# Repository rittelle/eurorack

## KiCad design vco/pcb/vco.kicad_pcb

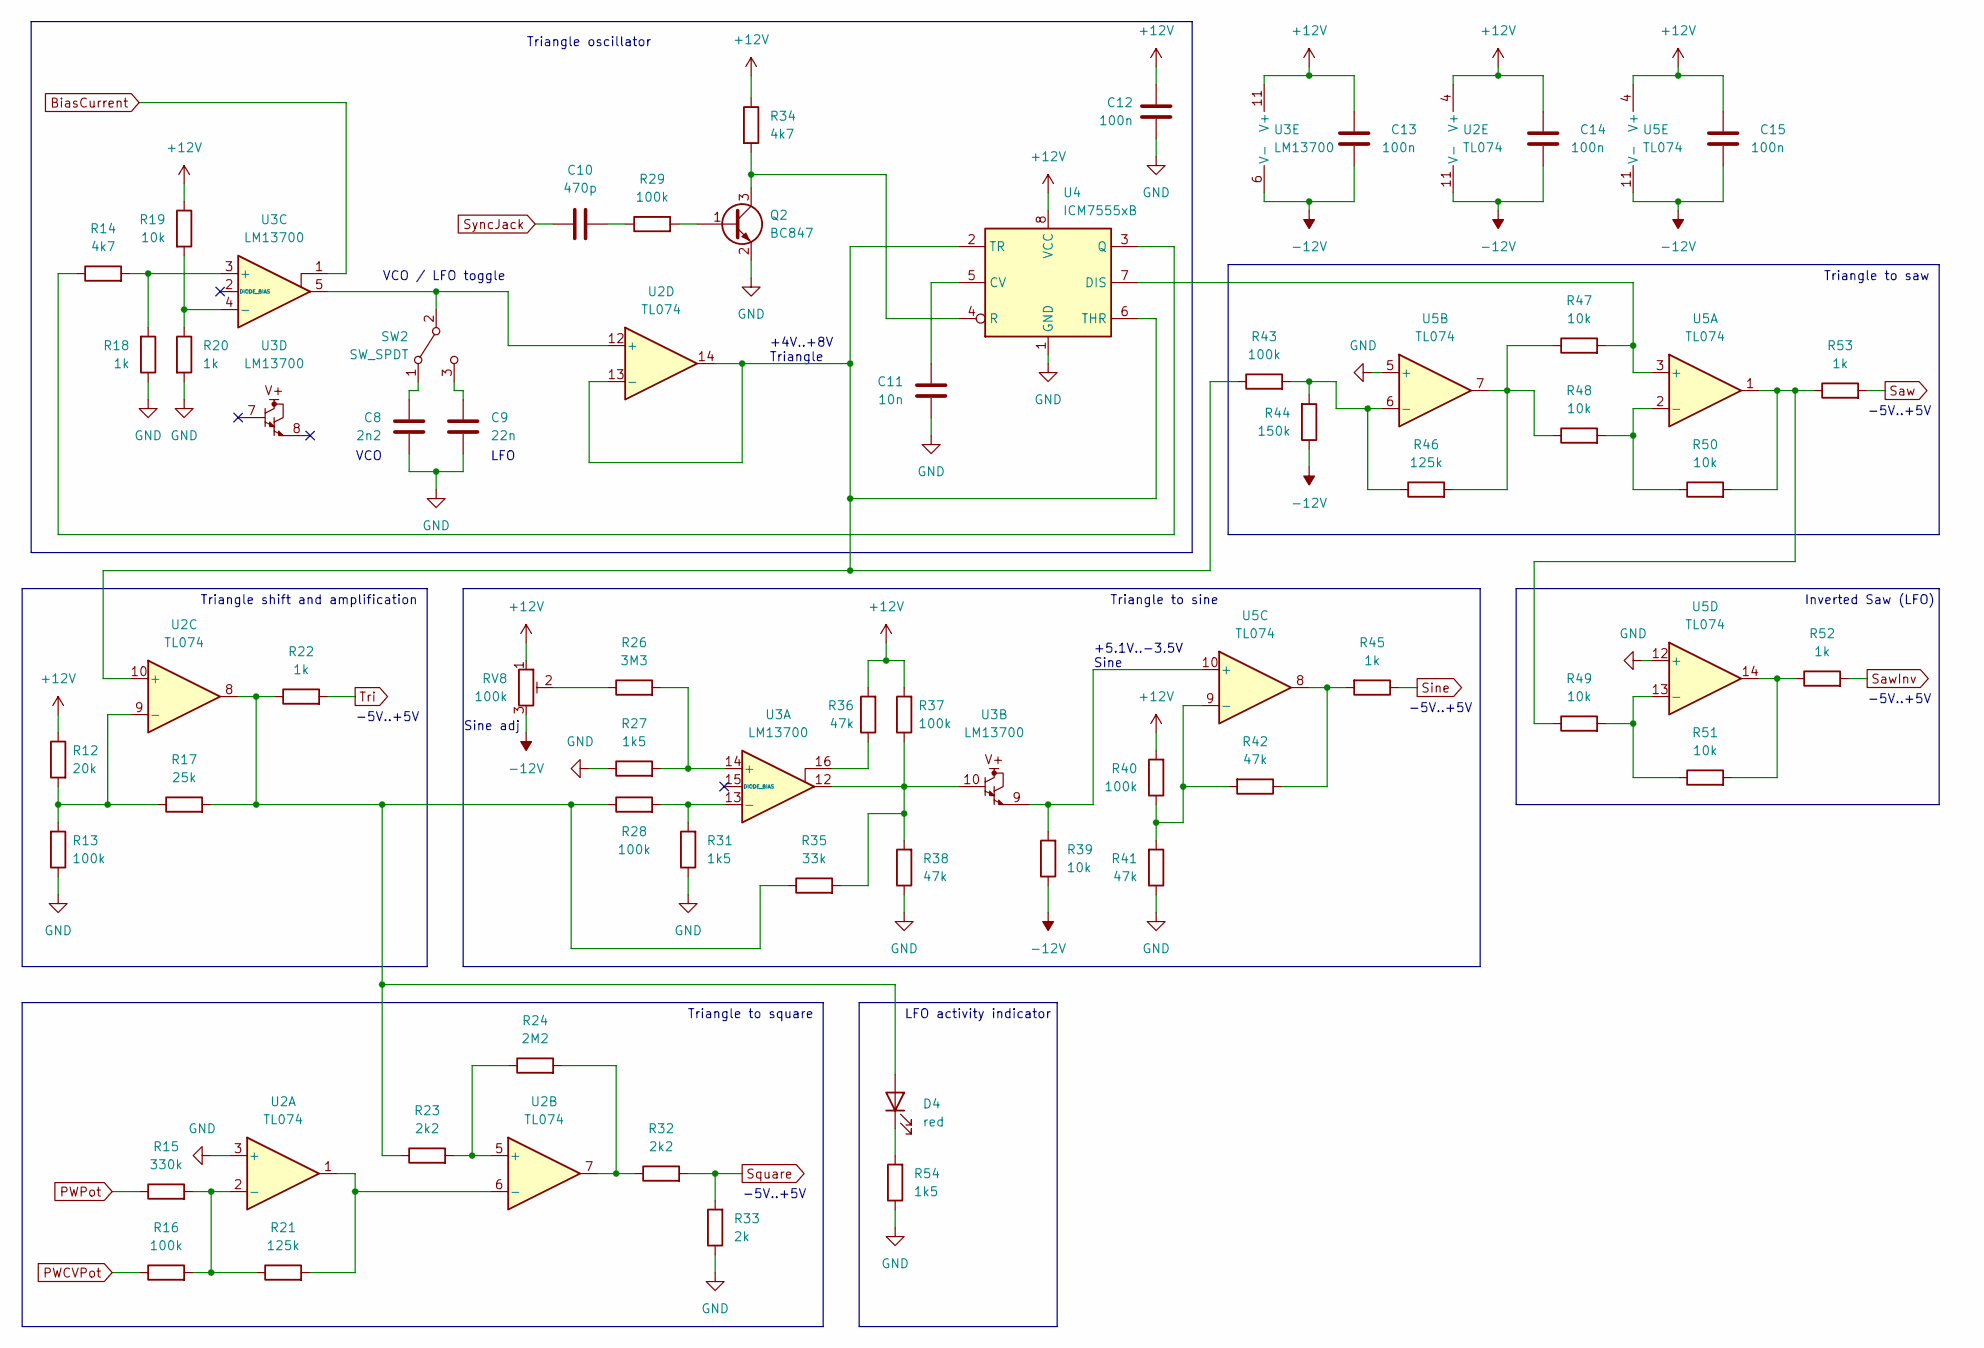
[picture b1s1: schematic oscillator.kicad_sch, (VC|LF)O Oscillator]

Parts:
C8: 2n2; C_0603_1608Metric_Pad1.08x0.95mm_HandSolder
C9: 22n; C_0603_1608Metric_Pad1.08x0.95mm_HandSolder
C10: 470p; C_0603_1608Metric_Pad1.08x0.95mm_HandSolder
C11: 10n; C_0603_1608Metric_Pad1.08x0.95mm_HandSolder
C12, C13, C14, C15: 100n; C_0603_1608Metric_Pad1.08x0.95mm_HandSolder
D4: red; LED_D3.0mm_FlatTop; Mouser 604-WP424IDT
Q2: BC847; SOT-23_Handsoldering; Mouser 771-BC847C-T/R
R12: 20k; R_0603_1608Metric_Pad0.98x0.95mm_HandSolder
R13, R16, R28, R29, R37, R40, R43: 100k; R_0603_1608Metric_Pad0.98x0.95mm_HandSolder
R14, R34: 4k7; R_0603_1608Metric_Pad0.98x0.95mm_HandSolder
R15: 330k; R_0603_1608Metric_Pad0.98x0.95mm_HandSolder
R17: 25k; R_0603_1608Metric_Pad0.98x0.95mm_HandSolder
R18, R20, R22, R45, R52, R53: 1k; R_0603_1608Metric_Pad0.98x0.95mm_HandSolder
R19, R39, R47, R48, R49, R50, R51: 10k; R_0603_1608Metric_Pad0.98x0.95mm_HandSolder
R21, R46: 125k; R_0603_1608Metric_Pad0.98x0.95mm_HandSolder
R23, R32: 2k2; R_0603_1608Metric_Pad0.98x0.95mm_HandSolder
R24: 2M2; R_0603_1608Metric_Pad0.98x0.95mm_HandSolder
R26: 3M3; R_0603_1608Metric_Pad0.98x0.95mm_HandSolder
R27, R31, R54: 1k5; R_0603_1608Metric_Pad0.98x0.95mm_HandSolder
R33: 2k; R_0603_1608Metric_Pad0.98x0.95mm_HandSolder
R35: 33k; R_0603_1608Metric_Pad0.98x0.95mm_HandSolder
R36, R38, R41, R42: 47k; R_0603_1608Metric_Pad0.98x0.95mm_HandSolder
R44: 150k; R_0603_1608Metric_Pad0.98x0.95mm_HandSolder
RV8: 100k; Potentiometer_Bourns_3296W_Vertical
SW2: SW_SPDT; Switch_Sub-Minitiature_Vertical
U2, U5: TL074; SOIC-14_3.9x8.7mm_P1.27mm; Mouser 595-TL074CDR
U3: LM13700; SOIC-16_3.9x9.9mm_P1.27mm; Mouser 926-LM13700MX/NOPB
U4: ICM7555xB; SOIC-8_3.9x4.9mm_P1.27mm; Mouser 968-ICM7555IBAZ-T

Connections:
+12V: C12.2, C13.1, C14.1, C15.1, R12.1, R19.1, R34.1, R36.2, R37.2, R40.2, RV8.1, U2.4 (V+), U3.11 (V+), U4.8 (VCC), U5.4 (V+); also elsewhere on the board
-12V: C13.2, C14.2, C15.2, R39.1, R44.1, RV8.3, U2.11 (V-), U3.6 (V-), U5.11 (V-); also elsewhere on the board
BiasCurrent: U3.1; also elsewhere on the board
GND: C8.1, C9.1, C11.1, C12.1, Q2.2 (E), R13.1, R18.1, R20.2, R27.1, R31.1, R33.1, R38.1, R41.1, R54.1, U2.3 (+), U4.1 (GND), U5.5 (+), U5.12 (+); also elsewhere on the board
unnamed: C8.2, SW2.1 (A)
unnamed: C9.2, SW2.3 (C)
unnamed: C10.1, R29.1
unnamed: C11.2, U4.5 (CV)
unnamed: D4.1 (K), R54.2
unnamed: D4.2 (A), R17.2, R22.1, R23.1, R28.1, R35.1, U2.8
unnamed: Q2.1 (B), R29.2
unnamed: Q2.3 (C), R34.2, U4.4 (R)
unnamed: R12.2, R13.2, R17.1, U2.9 (-)
unnamed: R14.1, U4.3 (Q)
unnamed: R14.2, R18.2, U3.3 (+)
unnamed: R15.2, R16.2, R21.1, U2.2 (-)
unnamed: R19.2, R20.1, U3.4 (-)
unnamed: R21.2, U2.1, U2.6 (-)
unnamed: R23.2, R24.1, U2.5 (+)
unnamed: R24.2, R32.1, U2.7
unnamed: R26.1, RV8.2
unnamed: R26.2, R27.2, U3.14 (+)
unnamed: R28.2, R31.2, U3.13 (-)
unnamed: R35.2, R37.1, R38.2, U3.10, U3.12
unnamed: R36.1, U3.16
unnamed: R39.2, U3.9, U5.10 (+)
unnamed: R40.1, R41.2, R42.2, U5.9 (-)
unnamed: R42.1, R45.2, U5.8
unnamed: R43.1, U2.10 (+), U2.13 (-), U2.14, U4.2 (TR), U4.6 (THR)
unnamed: R43.2, R44.2, R46.1, U5.6 (-)
unnamed: R46.2, R47.1, R48.1, U5.7
unnamed: R47.2, U4.7 (DIS), U5.3 (+)
unnamed: R48.2, R50.1, U5.2 (-)
unnamed: R49.1, R50.2, R53.1, U5.1
unnamed: R49.2, R51.1, U5.13 (-)
unnamed: R51.2, R52.1, U5.14
unnamed: SW2.2 (B), U2.12 (+), U3.5
PWCVPot: R16.1; also elsewhere on the board
PWPot: R15.1; also elsewhere on the board
Saw: R53.2; also elsewhere on the board
SawInv: R52.2; also elsewhere on the board
Sine: R45.1; also elsewhere on the board
Square: R32.2, R33.2; also elsewhere on the board
SyncJack: C10.2; also elsewhere on the board
Tri: R22.2; also elsewhere on the board

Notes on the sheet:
-5V..+5V
Triangle shift and amplification
Triangle to square
Sine adj
Inverted Saw (LFO)
+5.1V..-3.5V Sine
+4V..+8V Triangle
Triangle oscillator
LFO activity indicator
VCO / LFO toggle
Triangle to saw
VCO
LFO
Triangle to sine

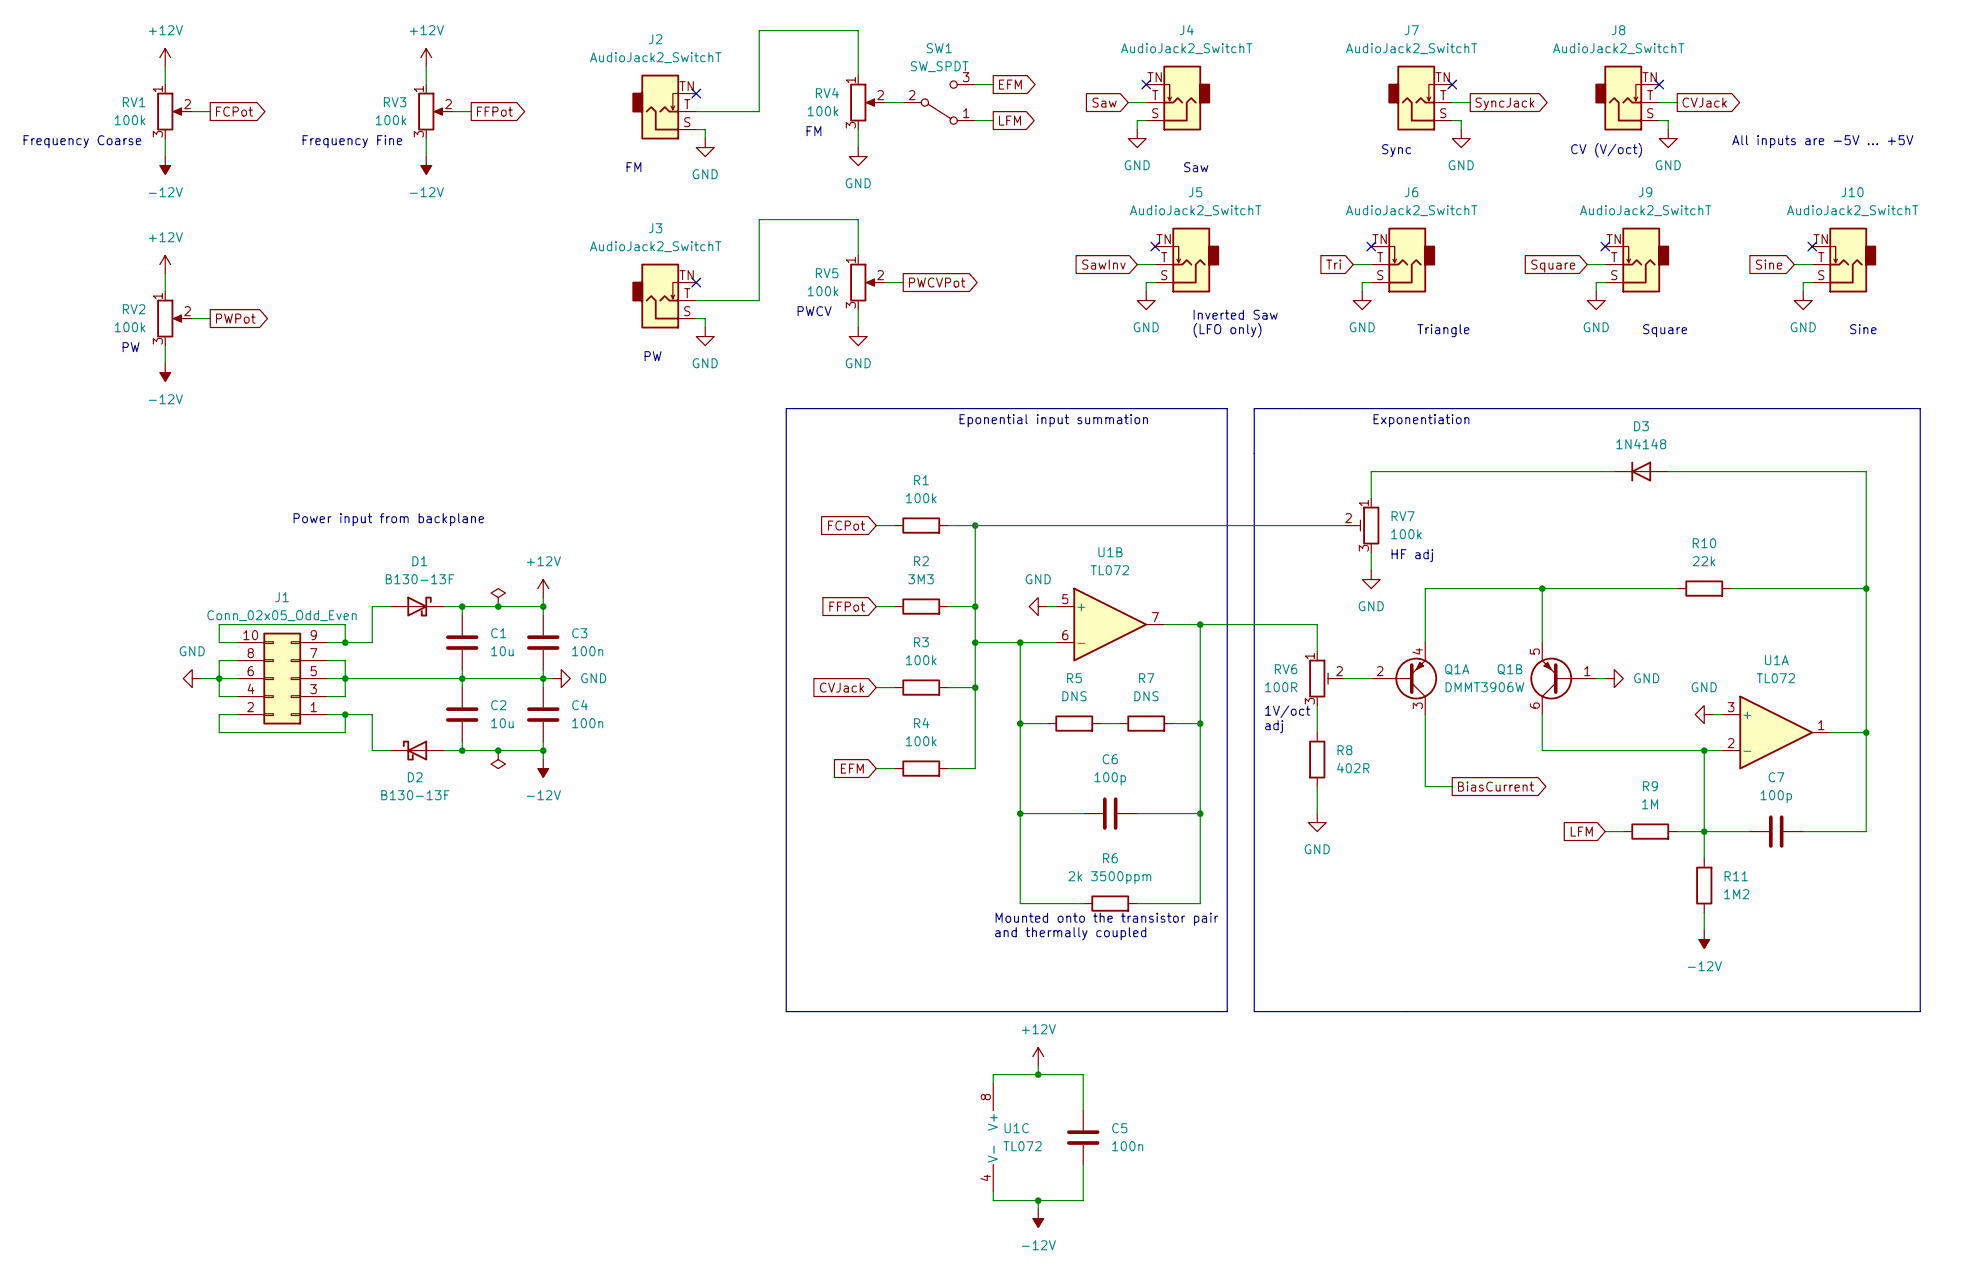
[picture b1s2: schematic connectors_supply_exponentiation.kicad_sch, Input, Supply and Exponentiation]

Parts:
C1, C2: 10u; C_0603_1608Metric_Pad1.08x0.95mm_HandSolder
C3, C4, C5: 100n; C_0603_1608Metric_Pad1.08x0.95mm_HandSolder
C6, C7: 100p; C_0603_1608Metric_Pad1.08x0.95mm_HandSolder
D1, D2: B130-13F; D_SMA_Handsoldering; Mouser 621-B130-F
D3: 1N4148; D_SOD-323_HandSoldering; Mouser 512-1N4148WS
J1: Conn_02x05_Odd_Even; PinHeader_2x05_P2.54mm_Vertical; Mouser 200-TSW10507GD
J2, J3, J4, J5, J6, J7, J8, J9, J10: AudioJack2_SwitchT; Jack_3.5mm_QingPu_WQP-PJ398SM_Vertical_CircularHoles
Q1: DMMT3906W; SOT-363_SC-70-6; Mouser 621-DMMT3906W-F
R1, R3, R4: 100k; R_0603_1608Metric_Pad0.98x0.95mm_HandSolder
R2: 3M3; R_0603_1608Metric_Pad0.98x0.95mm_HandSolder
R5, R7: DNS; R_0603_1608Metric_Pad0.98x0.95mm_HandSolder
R6: 2k 3500ppm; R_Axial_DIN0309_L9.0mm_D3.2mm_P15.24mm_Horizontal
R8: 402R; R_0603_1608Metric_Pad0.98x0.95mm_HandSolder
R9: 1M; R_0603_1608Metric_Pad0.98x0.95mm_HandSolder
R10: 22k; R_0603_1608Metric_Pad0.98x0.95mm_HandSolder
R11: 1M2; R_0603_1608Metric_Pad0.98x0.95mm_HandSolder
RV1, RV2, RV3, RV4, RV5: 100k; Potentiometer_Alpha_RD901F-40-00D_Single_Vertical
RV6: 100R; Potentiometer_Bourns_3296W_Vertical
RV7: 100k; Potentiometer_Bourns_3296W_Vertical
SW1: SW_SPDT; Switch_Sub-Minitiature_Vertical
U1: TL072; SOIC-8_3.9x4.9mm_P1.27mm; Mouser 595-TL072CDR

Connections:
+12V: C1.1, C3.1, C5.1, D1.1 (K), RV1.1, RV2.1, RV3.1, U1.8 (V+); also elsewhere on the board
-12V: C2.2, C4.2, C5.2, D2.2 (A), R11.1, RV1.3, RV2.3, RV3.3, U1.4 (V-); also elsewhere on the board
BiasCurrent: Q1.3 (C1); also elsewhere on the board
CVJack: J8.T, R3.1
EFM: R4.1, SW1.3 (C)
FCPot: R1.1, RV1.2
FFPot: R2.1, RV3.2
GND: C1.2, C2.1, C3.2, C4.1, J1.3, J1.4, J1.5, J1.6, J1.7, J1.8, J2.S, J3.S, J4.S, J5.S, J6.S, J7.S, J8.S, J9.S, J10.S, Q1.1 (B2), R8.2, RV4.3, RV5.3, RV7.3, U1.3 (+), U1.5 (+); also elsewhere on the board
LFM: R9.1, SW1.1 (A)
unnamed: C6.1, R1.2, R2.2, R3.2, R4.2, R5.1, R6.1, RV7.2, U1.6 (-)
unnamed: C6.2, R6.2, R7.2, RV6.1, U1.7
unnamed: C7.1, Q1.6 (C2), R9.2, R11.2, U1.2 (-)
unnamed: C7.2, D3.2 (A), R10.2, U1.1
unnamed: D1.2 (A), J1.9, J1.10
unnamed: D2.1 (K), J1.1, J1.2
unnamed: D3.1 (K), RV7.1
unnamed: J2.T, RV4.1
unnamed: J3.T, RV5.1
unnamed: Q1.2 (B1), RV6.2
unnamed: Q1.4 (E1), Q1.5 (E2), R10.1
unnamed: R5.2, R7.1
unnamed: R8.1, RV6.3
unnamed: RV4.2, SW1.2 (B)
PWCVPot: RV5.2; also elsewhere on the board
PWPot: RV2.2; also elsewhere on the board
Saw: J4.T; also elsewhere on the board
SawInv: J5.T; also elsewhere on the board
Sine: J10.T; also elsewhere on the board
Square: J9.T; also elsewhere on the board
SyncJack: J7.T; also elsewhere on the board
Tri: J6.T; also elsewhere on the board

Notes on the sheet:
Frequency Coarse
HF adj
1V/oct adj
Triangle
Power input from backplane
Inverted Saw (LFO only)
Mounted onto the transistor pair and thermally coupled
Eponential input summation
Saw
Square
Sync
Exponentiation
Frequency Fine
Sine
CV (V/oct)
PWCV
All inputs are -5V … +5V

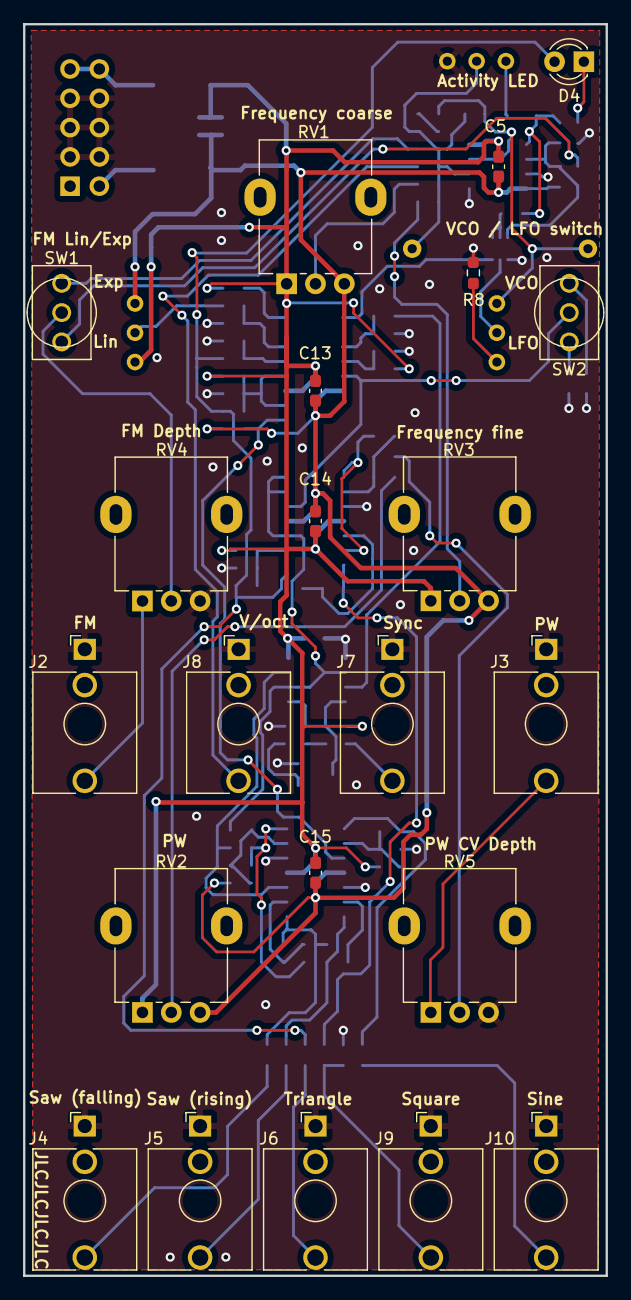
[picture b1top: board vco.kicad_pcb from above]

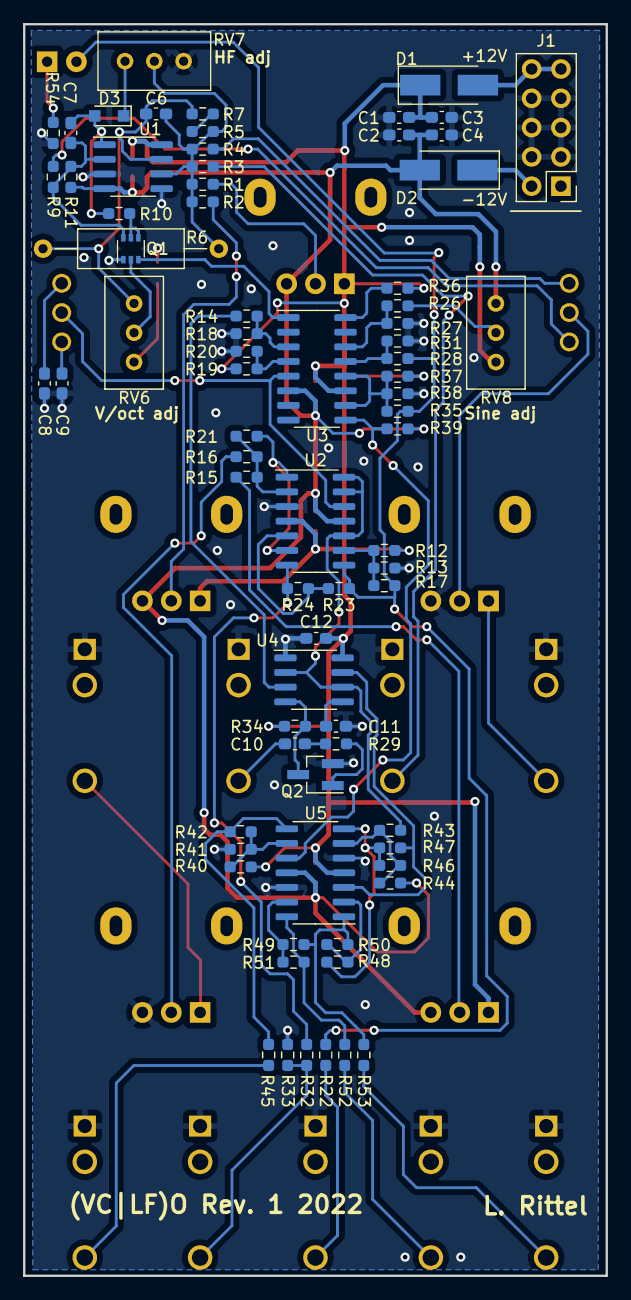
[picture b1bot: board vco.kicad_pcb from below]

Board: 2 copper layers, 50.5 x 108.5 mm, 98 parts (76 on the bottom side), 64 nets.

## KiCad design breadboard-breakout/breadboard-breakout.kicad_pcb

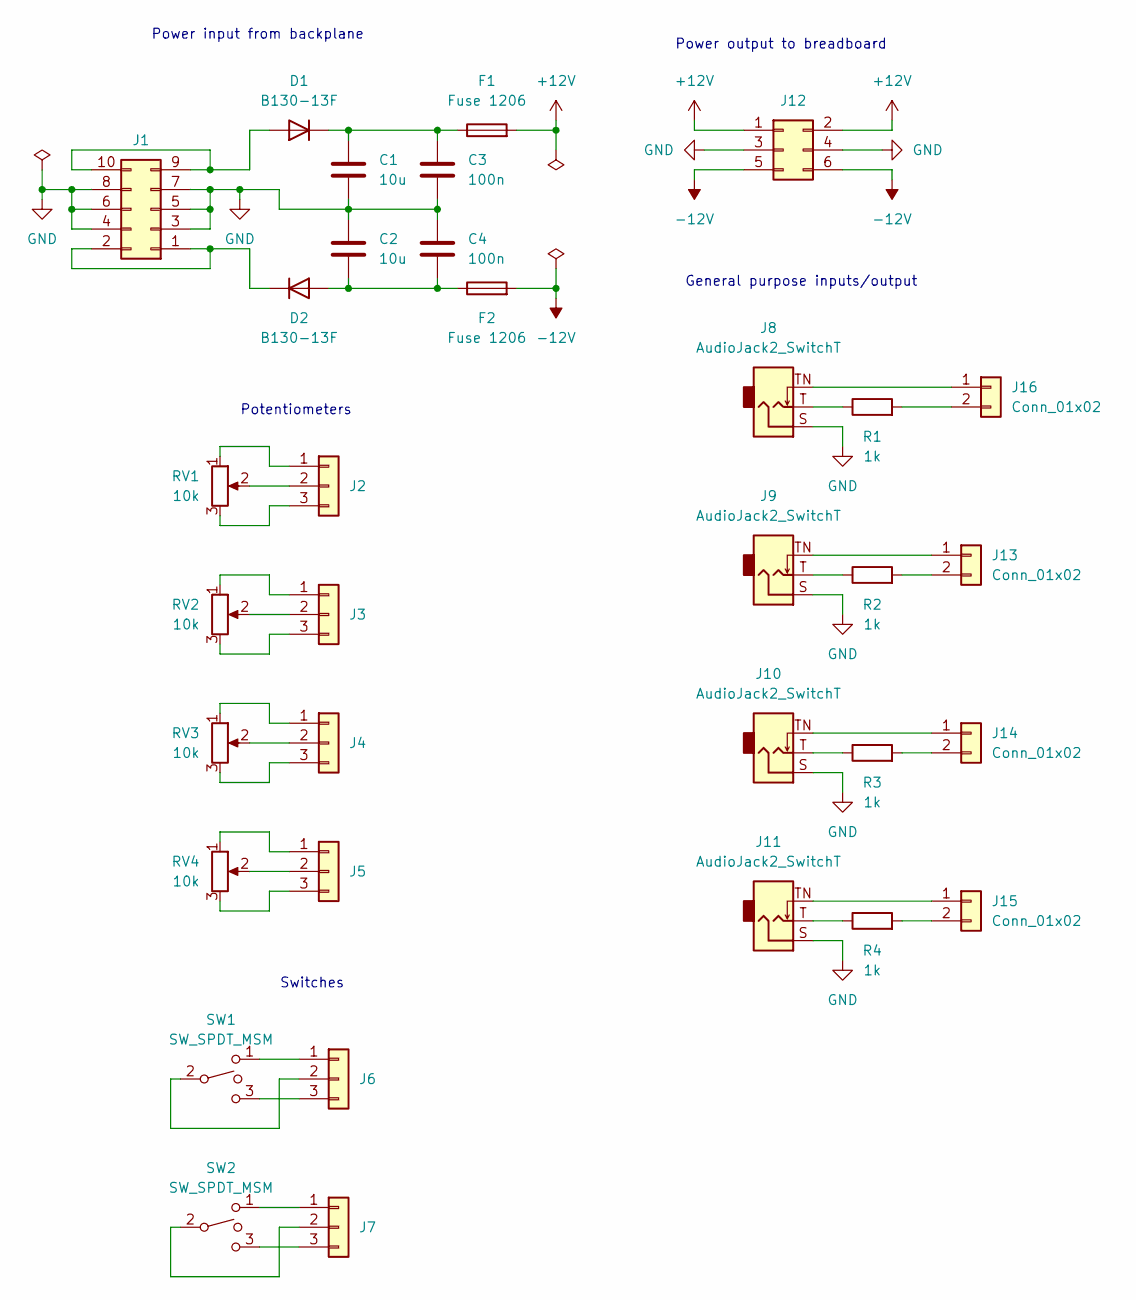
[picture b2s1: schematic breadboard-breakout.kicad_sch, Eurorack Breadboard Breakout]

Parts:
C1, C2: 10u; C_0603_1608Metric_Pad1.08x0.95mm_HandSolder
C3, C4: 100n; C_0603_1608Metric_Pad1.08x0.95mm_HandSolder
D1, D2: B130-13F; D_SMA_Handsoldering
F1, F2: Fuse 1206; Fuse_1206_3216Metric_Pad1.42x1.75mm_HandSolder
J1: Conn_02x05_Odd_Even; PinHeader_2x05_P2.54mm_Vertical
J2, J3, J4, J5, J6, J7: Conn_01x03; PinSocket_1x03_P2.54mm_Vertical
J8, J9, J10, J11: AudioJack2_SwitchT; Jack_3.5mm_QingPu_WQP-PJ398SM_Vertical_CircularHoles
J12: Conn_02x03_Odd_Even; PinSocket_2x03_P2.54mm_Vertical
J13, J14, J15, J16: Conn_01x02; PinSocket_1x02_P2.54mm_Vertical
R1, R2, R3, R4: 1k; R_0603_1608Metric_Pad0.98x0.95mm_HandSolder
RV1, RV2, RV3, RV4: 10k; Potentiometer_Alpha_RD901F-40-00D_Single_Vertical
SW1, SW2: SW_SPDT_MSM; Switch_Sub-Minitiature_Vertical

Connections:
+12V: F1.2, J12.1, J12.2
-12V: F2.2, J12.5, J12.6
GND: C1.2, C2.1, C3.2, C4.1, J1.3, J1.4, J1.5, J1.6, J1.7, J1.8, J8.S, J9.S, J10.S, J11.S, J12.3, J12.4
unnamed: C1.1, C3.1, D1.1 (K), F1.1
unnamed: C2.2, C4.2, D2.2 (A), F2.1
unnamed: D1.2 (A), J1.9, J1.10
unnamed: D2.1 (K), J1.1, J1.2
unnamed: J2.1, RV1.1
unnamed: J2.2, RV1.2
unnamed: J2.3, RV1.3
unnamed: J3.1, RV2.1
unnamed: J3.2, RV2.2
unnamed: J3.3, RV2.3
unnamed: J4.1, RV3.1
unnamed: J4.2, RV3.2
unnamed: J4.3, RV3.3
unnamed: J5.1, RV4.1
unnamed: J5.2, RV4.2
unnamed: J5.3, RV4.3
unnamed: J6.1, SW1.1
unnamed: J6.2, SW1.2
unnamed: J6.3, SW1.3
unnamed: J7.1, SW2.1
unnamed: J7.2, SW2.2
unnamed: J7.3, SW2.3
unnamed: J8.T, R1.1
unnamed: J9.T, R2.1
unnamed: J10.T, R3.1
unnamed: J10.TN, J14.1
unnamed: J11.T, R4.1
unnamed: J11.TN, J15.1
unnamed: J9.TN, J13.1
unnamed: J13.2, R2.2
unnamed: J14.2, R3.2
unnamed: J15.2, R4.2
unnamed: J8.TN, J16.1
unnamed: J16.2, R1.2

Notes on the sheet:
General purpose inputs/output
Power input from backplane
Power output to breadboard
Switches
Potentiometers

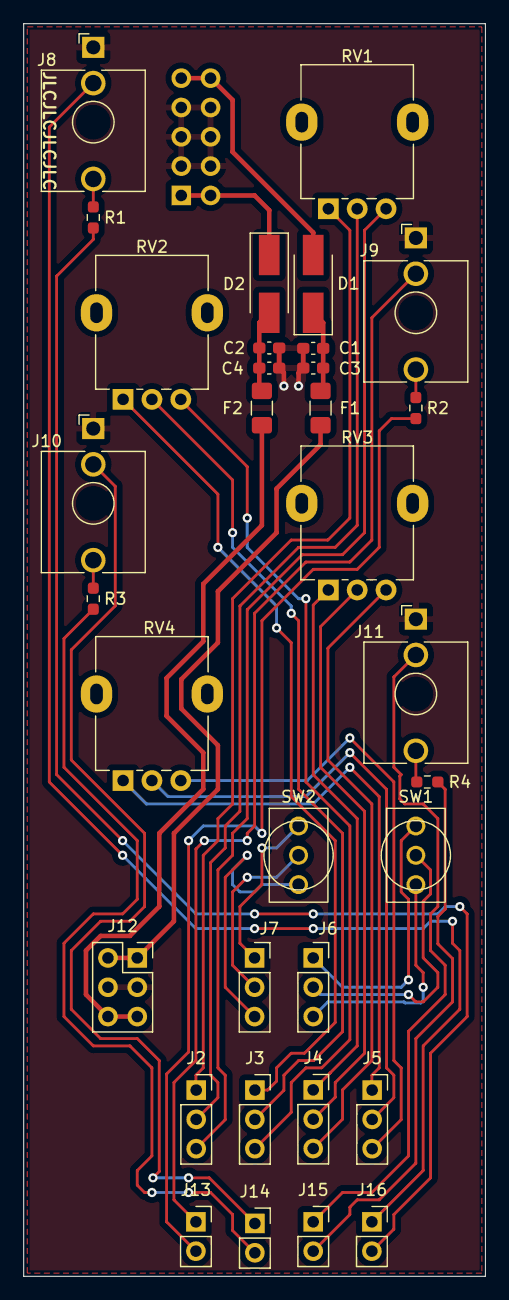
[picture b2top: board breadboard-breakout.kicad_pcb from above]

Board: 2 copper layers, 40.0 x 108.5 mm, 34 parts (1 on the bottom side), 37 nets.

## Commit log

2022-12-20 breadboard-breakout: add current WIP
2022-12-20 vco: add current WIP
2022-12-23 vco: Finish schematic
2022-12-23 vco: Add ltspice simulation
2022-12-23 Add .gitignore
2022-12-30 vco: Schematic update, footprints
    - small changes to the schematic
    - footprints assigned to all parts
2022-12-30 vco: some simulation
2022-12-30 vco: Added a (preliminery) list of stuff to buy
2022-12-30 vco: Add documentation on changes
2022-12-30 vco: Add output dividers for lfo operation
2022-12-30 vco: Undo the output dividers
2022-12-30 vco: Add a note about the CV input range
2022-12-30 vco: Add a VCO / LFO toggle switch
2022-12-30 vco: Start the PCB
    Position jacks, pots, switches and the led.
    Lock the UI elements.
2022-12-30 vco: Layout WIP: component placement
2022-12-30 vco: Layout
    Silkscreen still needs adjustment.
2022-12-30 vco: Layout fixes and dimensions
    Fixed the location of two pots and added dimensions to aid in front
    panel design.
2022-12-31 vco: Organize component markings
2022-12-31 vco: Add the project name on the PCB
2022-12-31 vco: Add Mouser order codes
    Add Mouser order codes to some parts. THis solution isn't really nice, though.
2022-12-31 vco: Add more info to silk
2022-12-31 vco: Update headers in pcb
2022-12-31 vco: Fix a link in the notes
2022-12-31 vco: Started a frontpanel design in KiCAD
2022-12-31 vco: Started a frontpanel design in Inkscape
2022-12-31 vco: Frontpanel Inkscape WIP
2022-12-31 vco: Finish frontpanel (for now)
2022-12-31 vco: Finished work on the front panel
2022-12-31 vco: Generate production files for the PCB
2022-12-31 vco: Add a BOM
    The parts from Thonkiconn are still missing.
2022-12-31 Add the gerber output directory to .gitignore
2022-12-31 vco: Update notes
2023-01-01 breakout: WIP
2023-01-01 vco: Small update
2023-01-01 breakout: Finish the PCB
2023-01-01 breakout: Start work on the front panel
2023-01-01 vco: Add note
2023-01-01 vco: Make the JLC order number text smaller
2023-01-01 breakout: Finalize the frontpanel
2023-01-01 breakout: finalize the pcb
2023-01-01 breakout: Add a copper layer
    Add a copper layer spanning the whole board.
2023-01-01 vco: Rotate the power connection on the pcb
2023-01-01 vco: Notes
2023-01-01 vco: re-generate the PCB gerber files
2023-01-01 vco: fix screw locations on the front panel
2023-01-02 breakout: add some notes
2023-01-02 vco: document some possible improvements
2023-01-03 Update the .gitignore
    Update the gitignore to properly include KiCad files that should not be
    in the repo. Removed the unnecessary .kicad_prl files.
2023-01-03 vco: add some possible improvements
2023-01-07 vco: Change some resistors to Exx values
    Some values didn't exist in any of ≤E96.
2023-01-07 Add a simulation of a diode VCO
2023-01-11 Allow LTSpice plot settings to be added
    Removed LTSpice plot settings (*.plt) from the .gitignore.
2023-01-11 Simulate an attenuverter in LTSpice
2023-01-12 vca: add a simulation of the mfos vca
    Add a ltspice simulation of Ray Wilson's VCA.
2023-01-12 Add a simulation on the LM13700 linearity
    Add a ltspice simulation that explores the linearity of the LM13700 with
    different diode bias currents.
2023-01-13 Simulate LM13700 datasheet Fig. 17 in ltspice
    This is a continuation of the linearity simulation which is removed.
2023-01-13 Add LTSpice net files to .gitignore
2023-01-13 Add unlinearized variant LM13700 datasheet simulation
    Add an unlinearized curcuit for comparison. Also create a plot settings
    file.
2023-01-15 breakout: update notes
2023-01-15 vca: add a sim to explore the LM13700's linearity
2023-04-09 vca: some vca simulations
    Do some simulations for VCA ideas in LTSpice.
2023-04-25 vca: add analog multiplication experiments
2023-04-25 vca: further ltspice simulations
    - vca does not work, yet
    - add a simulation for the characteristic of the LM13700, still buggy
2024-02-04 template: create a UI element template
    Add the following elements:
    - the front plates up to 20hp
    - small, medium knobs
    - audio i/o
    - switch
    - led
2024-02-04 vca: create a first ui mockup
2024-02-04 template: improve the ui template a bit
    - make it a bit easier to use
    - pre-create a layer for the frontpanel
2024-02-04 template: add a small knob without scales
    For a smaller size of the labeling.
2024-02-04 template: fix the height of the frontpanel
2024-02-04 vca: improve the idea for the one channel vca
2024-02-04 vca: move to a dual channel design (WIP)
